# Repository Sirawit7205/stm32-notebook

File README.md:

# STM32 Notebook

This is an STM32 dev board that is designed to be put on a B6 ring binder notebook as covers. The board size is 130x180mm and contains 21 4mm ring holes.

**Note: I did tried to follow best practices as much as possible while designing this board, but it is still intended to be used as a notebook cover. The devices fitted might not work to their fullest spec. Please exercise caution.**

## Features - Front

The front side is the devboard. Featuring:

 - An STM32F103ZCT6 ARM-Cortex M3 Microcontroller in a 144-pin LQFP package
 - External 16MHz crystal and 32.768kHz RTC crystal
 - 2x IRS2003 H-Bridge Drivers with a pair of IRF7403 MOSFET (total of 2 drivers)
 - 2x PM8834 MOSFET Drivers with two IRF7403 MOSFETs in an Open-Drain configuration (total of 4 drivers)
 - 2x CD4050 Buffer for translating higher voltage logic inputs into STM32's 3.3v logic (total of 8 inputs)
 - 40x IO pins breakout
 - BOOT0/BOOT1 headers
 - SWD headers
 - Reset button
 - LM2596S-3.3 Buck Converter
 - Cute ponies

## Features - Back

The back side is a PCB footprint reference guide. Featuring:

 - Passive components (0201 to 1206)
 - Electrolytic Capacitors (3mm to 10mm)
 - JST connectors (GH, SH, PH, ...)
 - Diodes (MELF, SMA, SMB, SOD123, SOD323, ...)
 - Diode Bridges (ABS, MBS)
 - Transistors (SOT23, SOT223, LFPAK56, DPAK, ...)
 - Crystals (HC49, 0603 to 7050, 2 and 4 pins versions)
 - SOICs (SOIC4, SOIC8, SOIC14, SOIC16)
 - Wide SOICs (SOIC8W to SOIC28W)
 - TSSOPs (TSSOP8 to TSSOP40)
 - QFPs 0.5mm pitch (LQFP32 to LQFP144)
 - DFNs 0.4mm and 0.5mm pitch (DFN6 to DFN44)
 - QFNs 0.4mm pitch (QFN20 to QFN76)
 - QFNs 0.5mm pitch (QFN12 to QFN72)
 - More cute ponies
 
 ## Features - Latch
 
 This board features a pair of 20-pin Slide-Lock FFP Connectors, one on each side. These connectors are there so you can add a 20-pin Same-Side FFC Cable to act as a notebook closing strap.
 
 ## Licenses
 
 Hardware is licensed under `SPDX-License-Identifier: Apache-2.0 WITH SHL-2.1`
 
 This project is a certified Open Source Hardware. OSHWA UID TH000006.
 https://certification.oshwa.org/th000006.html
 
 ## Credits

 - 3215 Crystal model by Sam Ma: https://grabcad.com/library/crystal-smd-3215-pin2-1
 - Inductor model by Gydius: https://grabcad.com/library/inductor-wurth-elektronik-74437324100-1

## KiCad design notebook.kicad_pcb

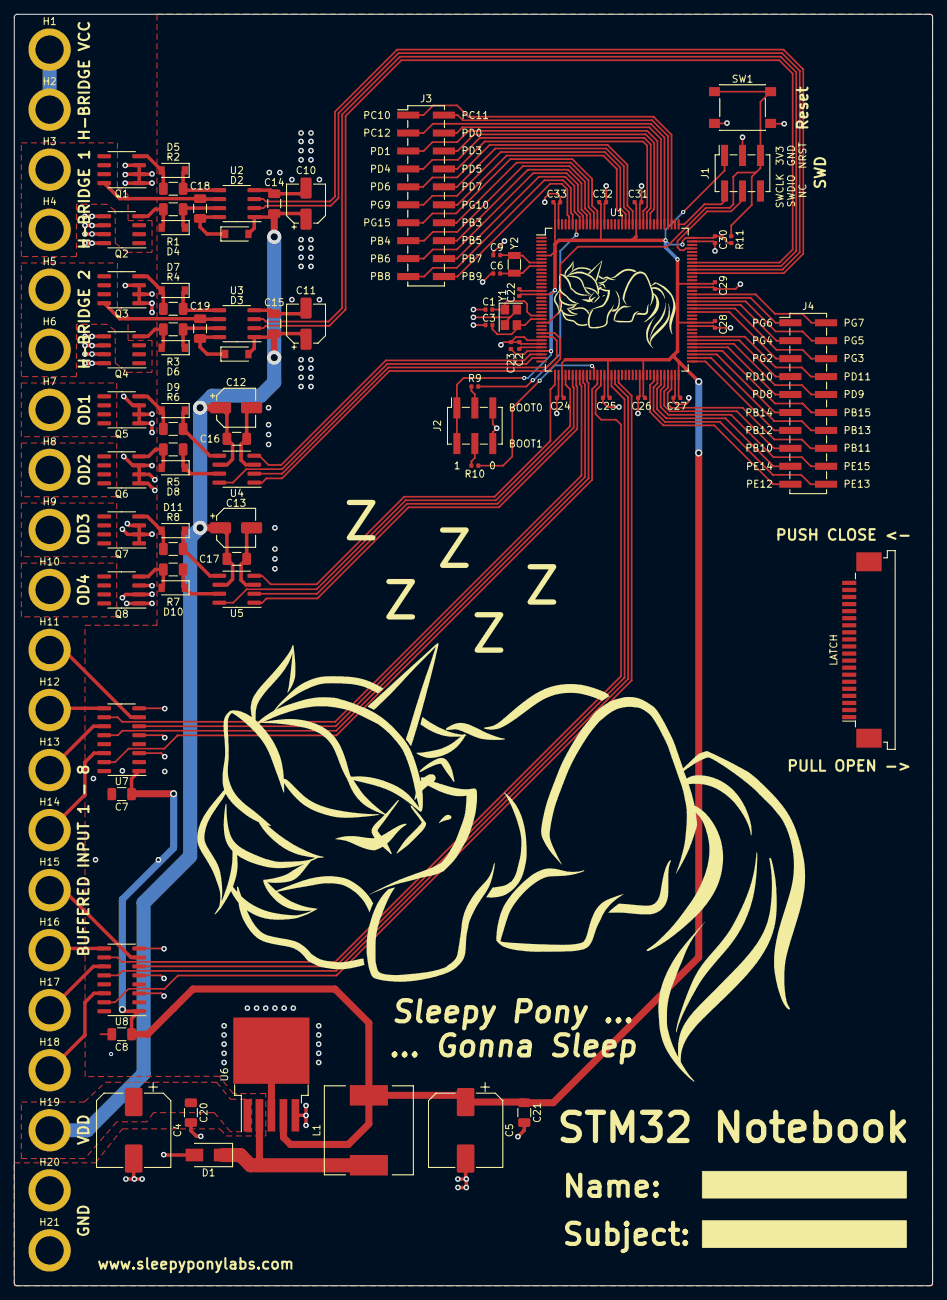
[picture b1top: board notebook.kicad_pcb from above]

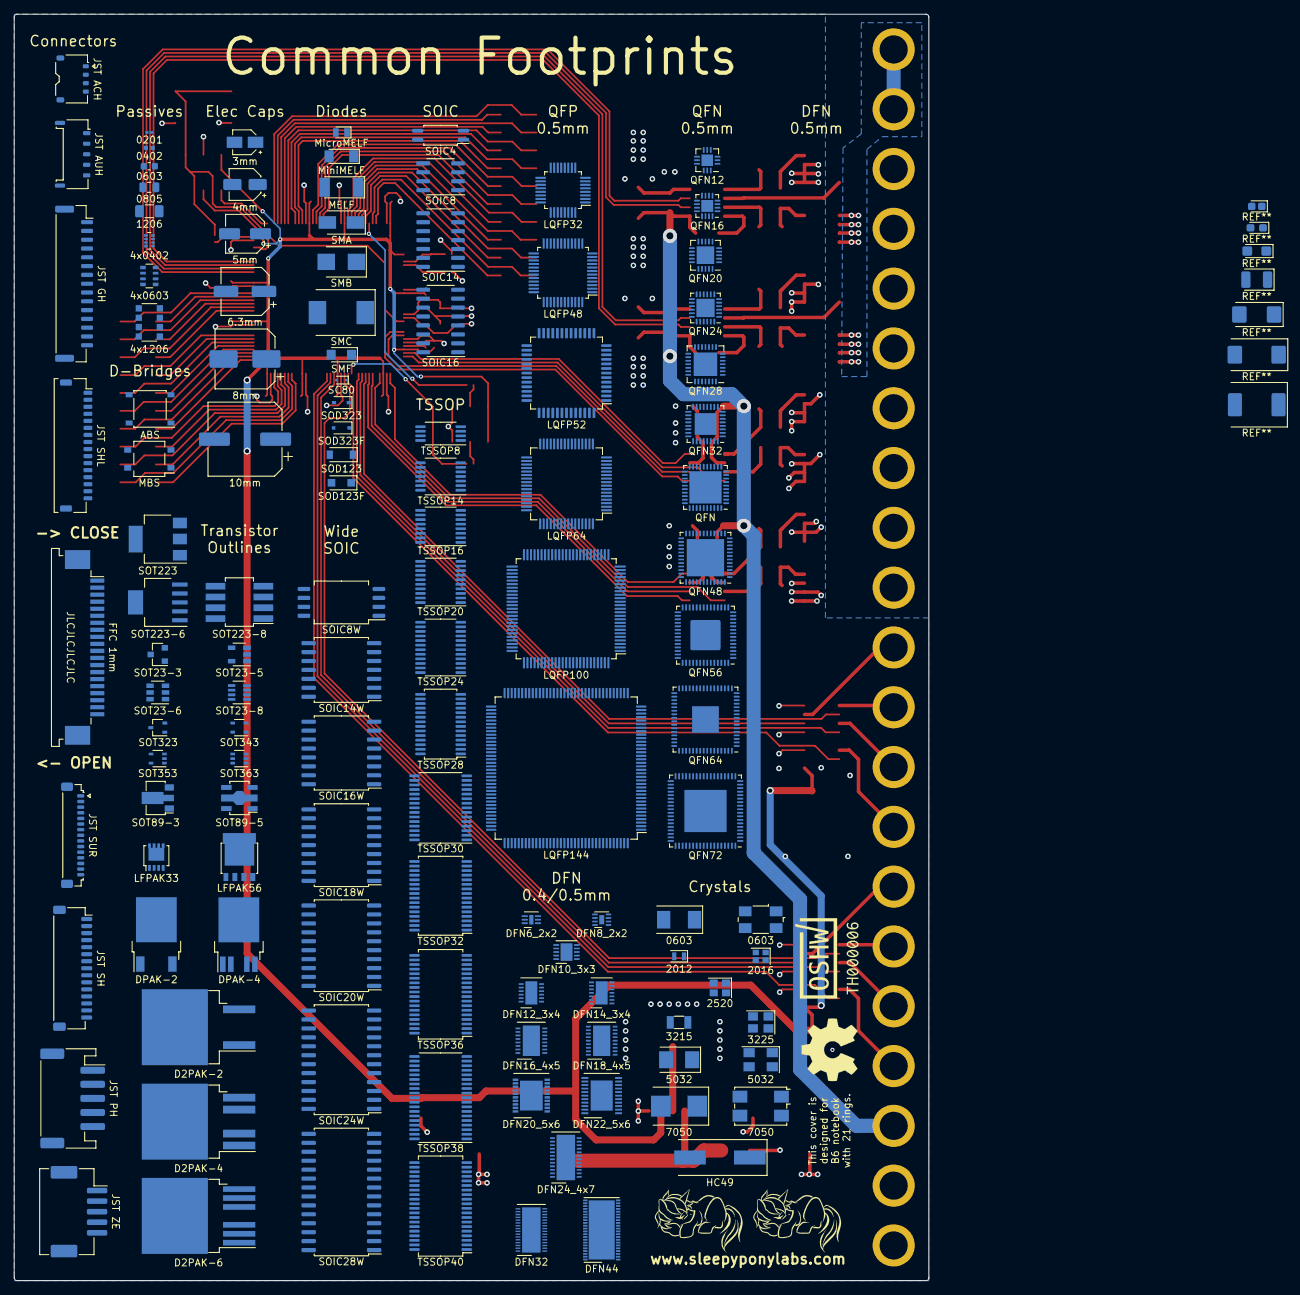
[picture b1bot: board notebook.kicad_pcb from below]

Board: 2 copper layers, 130.0 x 180.0 mm, 222 parts (121 on the bottom side), 109 nets.

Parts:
3mm: CP_Elec_3x5.3
4mm: CP_Elec_4x3
4x0402: R_Array_Convex_4x0402
4x0603: R_Array_Convex_4x0603
4x1206: R_Array_Convex_4x1206
5mm: CP_Elec_5x3
6.3mm: CP_Elec_6.3x3
8mm: CP_Elec_8x5.4
10mm: CP_Elec_10x7.7
0201: C_0201_0603Metric
0402: C_0402_1005Metric
0603: Crystal_SMD_0603-4Pin_6.0x3.5mm
0603#2: Crystal_SMD_0603-2Pin_6.0x3.5mm
0603#3: C_0603_1608Metric
0805: C_0805_2012Metric
1206: C_1206_3216Metric
2012: Crystal_SMD_2012-2Pin_2.0x1.2mm
2016: Crystal_SMD_2016-4Pin_2.0x1.6mm
2520: Crystal_SMD_2520-4Pin_2.5x2.0mm
3215: Crystal_SMD_3215-2Pin_3.2x1.5mm
3225: Crystal_SMD_3225-4Pin_3.2x2.5mm
5032: Crystal_SMD_5032-4Pin_5.0x3.2mm
5032#2: Crystal_SMD_5032-2Pin_5.0x3.2mm
7050: Crystal_SMD_7050-4Pin_7.0x5.0mm
7050#2: Crystal_SMD_7050-2Pin_7.0x5.0mm
ABS: Diode_Bridge_Diotec_ABS
C1, C3, C6, C9: 22pF; C_0402_1005Metric
C2: 10nF; C_0402_1005Metric
C4, C5: 220uF; CP_Elec_10x10
C7, C8, C14, C15, C16, C17, C20, C21: 100nF; C_1206_3216Metric
C10, C11, C12, C13: 10uF; CP_Elec_5x5.4
C18, C19: 1uF; C_1206_3216Metric
C22, C23, C24, C25, C26, C27, C28, C29, C30, C31, C32, C33: 100nF; C_0402_1005Metric
D1: SS34; D_SMA
D2, D3: FR107; D_SOD-123
D2PAK-2: TO-263-2
D2PAK-4: TO-263-4
D2PAK-6: TO-263-6
D4, D5, D6, D7, D8, D9, D10, D11: 1N4148; D_SOD-123
DFN6_2x2: DFN-6-1EP_2x2mm_P0.5mm_EP0.6x1.37mm
DFN8_2x2: DFN-8-1EP_2x2mm_P0.5mm_EP0.7x1.3mm
DFN10_3x3: DFN-10-1EP_3x3mm_P0.5mm_EP1.7x2.5mm
DFN12_3x4: DFN-12-1EP_3x4mm_P0.5mm_EP1.7x3.3mm
DFN14_3x4: DFN-14-1EP_3x4mm_P0.5mm_EP1.7x3.3mm
DFN16_4x5: DFN-16-1EP_4x5mm_P0.5mm_EP2.44x4.34mm
DFN18_4x5: DFN-18-1EP_4x5mm_P0.5mm_EP2.44x4.34mm
DFN20_5x6: DFN-20-1EP_5x6mm_P0.5mm_EP3.24x4.24mm
DFN22_5x6: DFN-22-1EP_5x6mm_P0.5mm_EP3.14x4.3mm
DFN24_4x7: DFN-24-1EP_4x7mm_P0.5mm_EP2.64x6.44mm
DFN32: DFN-32-1EP_4x7mm_P0.4mm_EP2.64x6.44mm
DFN44: DFN-44-1EP_5x8.9mm_P0.4mm_EP3.7x8.4mm
DPAK-2: TO-252-2
DPAK-4: TO-252-4
FFC 1mm: TE_2-84952-0_1x20-1MP_P1.0mm_Horizontal
H1, H2: VCCin; MountingHole_4mm_Pad_Thin
H3: HB1OUT1; MountingHole_4mm_Pad_Thin
H4: HB1OUT2; MountingHole_4mm_Pad_Thin
H5: HB2OUT1; MountingHole_4mm_Pad_Thin
H6: HB2OUT2; MountingHole_4mm_Pad_Thin
H7: OD1OUT; MountingHole_4mm_Pad_Thin
H8: OD2OUT; MountingHole_4mm_Pad_Thin
H9: OD3OUT; MountingHole_4mm_Pad_Thin
H10: OD4OUT; MountingHole_4mm_Pad_Thin
H11: ISOIN1; MountingHole_4mm_Pad_Thin
H12: ISOIN2; MountingHole_4mm_Pad_Thin
H13: ISOIN3; MountingHole_4mm_Pad_Thin
H14: ISOIN4; MountingHole_4mm_Pad_Thin
H15: ISOIN5; MountingHole_4mm_Pad_Thin
H16: ISOIN6; MountingHole_4mm_Pad_Thin
H17: ISOIN7; MountingHole_4mm_Pad_Thin
H18: ISOIN8; MountingHole_4mm_Pad_Thin
H19: VDDin; MountingHole_4mm_Pad_Thin
H20, H21: GND; MountingHole_4mm_Pad_Thin
HC49: Crystal_SMD_HC49-SD
J1: SWD; PinSocket_2x03_P2.54mm_Vertical_SMD
J2: BOOT; PinSocket_2x03_P2.54mm_Vertical_SMD
J3: ConnA; PinHeader_2x10_P2.54mm_Vertical_SMD
J4: ConnB; PinHeader_2x10_P2.54mm_Vertical_SMD
JST ACH: JST_ACH_BM04B-ACHSS-A-GAN-ETF_1x04-1MP_P1.20mm_Ve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; JST_ACH_BM04B-ACHSS-A-GAN-ETF_1x04-1MP_P1.20mm_Vertical
JST AUH: JST_AUH_BM05B-AUHKS-GA-TB_1x05-1MP_P1.50mm_Vertic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; JST_AUH_BM05B-AUHKS-GA-TB_1x05-1MP_P1.50mm_Vertical
JST GH: JST_GH_SM15B-GHS-TB_1x15-1MP_P1.25mm_Horizontal
JST PH: JST_PH_S5B-PH-SM4-TB_1x05-1MP_P2.00mm_Horizontal
JST SH: JST_SH_SM15B-SRSS-TB_1x15-1MP_P1.00mm_Horizontal
JST SHL: JST_SHL_SM16B-SHLS-TF_1x16-1MP_P1.00mm_Horizontal
JST SUR: JST_SUR_SM15B-SURS-TF_1x15-1MP_P0.80mm_Horizontal
JST ZE: JST_ZE_SM05B-ZESS-TB_1x05-1MP_P1.50mm_Horizontal
L1: 33uH; L_12x12mm_H8mm
LATCH: TE_2-84952-0_1x20-1MP_P1.0mm_Horizontal
LFPAK33: LFPAK33
LFPAK56: LFPAK56
LQFP32: LQFP-32_5x5mm_P0.5mm
LQFP48: LQFP-48_7x7mm_P0.5mm
LQFP52: LQFP-52_10x10mm_P0.65mm
LQFP64: LQFP-64_10x10mm_P0.5mm
LQFP100: LQFP-100_14x14mm_P0.5mm
LQFP144: LQFP-144_20x20mm_P0.5mm
MBS: TO-269AA
MELF: D_MELF
MicroMELF: D_MicroMELF
MiniMELF: D_MiniMELF
Q1, Q2, Q3, Q4, Q5, Q6, Q7, Q8: IRF7403; SOIC-8_3.9x4.9mm_P1.27mm
QFN: QFN-40-1EP_6x6mm_P0.5mm_EP4.6x4.6mm
QFN12: QFN-12-1EP_3x3mm_P0.5mm_EP1.65x1.65mm
QFN16: QFN-16-1EP_3x3mm_P0.5mm_EP1.7x1.7mm
QFN20: QFN-20-1EP_4x4mm_P0.5mm_EP2.5x2.5mm
QFN24: QFN-24-1EP_4x4mm_P0.5mm_EP2.6x2.6mm
QFN28: QFN-28-1EP_5x5mm_P0.5mm_EP3.35x3.35mm
QFN32: QFN-32-1EP_5x5mm_P0.5mm_EP3.1x3.1mm
QFN48: QFN-48-1EP_7x7mm_P0.5mm_EP5.3x5.3mm
QFN56: QFN-56-1EP_8x8mm_P0.5mm_EP4.3x4.3mm
QFN64: QFN-64-1EP_9x9mm_P0.5mm_EP3.8x3.8mm
QFN72: QFN-72-1EP_10x10mm_P0.5mm_EP6x6mm
R1, R2, R3, R4, R5, R6, R7, R8: 22R; R_1206_3216Metric
R9, R10, R11: 10K; R_0402_1005Metric
Ref**: Val**; TH000006_svg2sz
SC80: D_SC-80
SMA: D_SMA
SMB: D_SMB
SMC: D_SMC
SMF: D_SMF
SOD123: D_SOD-123
SOD123F: D_SOD-123F
SOD323: D_SOD-323
SOD323F: D_SOD-323F
SOIC4: SOIC-4_4.55x2.6mm_P1.27mm
SOIC8: SOIC-8_3.9x4.9mm_P1.27mm
SOIC8W: SOIC-8_7.5x5.85mm_P1.27mm
SOIC14: SOIC-14_3.9x8.7mm_P1.27mm
SOIC14W: SOIC-14W_7.5x9mm_P1.27mm
SOIC16: SOIC-16_3.9x9.9mm_P1.27mm
SOIC16W: SOIC-16W_7.5x10.3mm_P1.27mm
SOIC18W: SOIC-18W_7.5x11.6mm_P1.27mm
SOIC20W: SOIC-20W_7.5x12.8mm_P1.27mm
SOIC24W: SOIC-24W_7.5x15.4mm_P1.27mm
SOIC28W: SOIC-28W_7.5x17.9mm_P1.27mm
SOT23-3: SOT-23
SOT23-5: SOT-23-5
SOT23-6: SOT-23-6
SOT23-8: SOT-23-8
SOT89-3: SOT-89-3
SOT89-5: SOT-89-5
SOT223: SOT-223
SOT223-6: SOT-223-6
SOT223-8: SOT-223-8
SOT323: SOT-323_SC-70
SOT343: SOT-343_SC-70-4
SOT353: SOT-353_SC-70-5
SOT363: SOT-363_SC-70-6
SW1: RESET; SW_SPST_PTS645
TSSOP8: TSSOP-8_4.4x3mm_P0.65mm
TSSOP14: TSSOP-14_4.4x5mm_P0.65mm
TSSOP16: TSSOP-16_4.4x5mm_P0.65mm
TSSOP20: TSSOP-20_4.4x6.5mm_P0.65mm
TSSOP24: TSSOP-24_4.4x7.8mm_P0.65mm
TSSOP28: TSSOP-28_4.4x9.7mm_P0.65mm
TSSOP30: TSSOP-30_6.1x9.7mm_P0.65mm
TSSOP32: TSSOP-32_6.1x11mm_P0.65mm
TSSOP36: TSSOP-36_6.1x12.5mm_P0.65mm
TSSOP38: TSSOP-38_6.1x12.5mm_P0.65mm
TSSOP40: TSSOP-40_6.1x14mm_P0.65mm
U1: STM32F103ZCT6; LQFP-144_20x20mm_P0.5mm
U2, U3: IRS2003; SOIC-8_3.9x4.9mm_P1.27mm
U4, U5: PM8834; SOIC-8_3.9x4.9mm_P1.27mm
U6: LM2596S-3.3; TO-263-5_TabPin3
U7, U8: 4050; SOIC-16_3.9x9.9mm_P1.27mm
Y1: 16MHz; Crystal_SMD_3225-4Pin_3.2x2.5mm
Y2: 32.768kHz; Crystal_SMD_3215-2Pin_3.2x1.5mm

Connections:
+3V3: C5.1, C7.1, C8.1, C21.1, C22.1, C23.1, C24.1, C25.1, C26.1, C27.1, C28.1, C29.1, C30.1, C31.1, C32.1, C33.1, J1.1, J2.1, J2.2, L1.2, R11.1, U1.6, U1.17, U1.33, U1.39, U1.52, U1.62, U1.72, U1.84, U1.95, U1.108, U1.121, U1.131, U1.144, U6.4, U7.1, U8.1
BOOT0: R9.2, U1.138
BOOT1: R10.1, U1.48
CA1: J3.1, U1.111
CA2: J3.2, U1.112
CA3: J3.3, U1.113
CA4: J3.4, U1.114
CA5: J3.5, U1.115
CA6: J3.6, U1.117
CA7: J3.7, U1.118
CA8: J3.8, U1.119
CA9: J3.9, U1.122
CA10: J3.10, U1.123
CA11: J3.11, U1.124
CA12: J3.12, U1.125
CA13: J3.13, U1.132
CA14: J3.14, U1.133
CA15: J3.15, U1.134
CA16: J3.16, U1.135
CA17: J3.17, U1.136
CA18: J3.18, U1.137
CA19: J3.19, U1.139
CA20: J3.20, U1.140
CB1: J4.1, U1.91
CB2: J4.2, U1.92
CB3: J4.3, U1.89
CB4: J4.4, U1.90
CB5: J4.5, U1.87
CB6: J4.6, U1.88
CB7: J4.7, U1.79
CB8: J4.8, U1.80
CB9: J4.9, U1.77
CB10: J4.10, U1.78
CB11: J4.11, U1.75
CB12: J4.12, U1.76
CB13: J4.13, U1.73
CB14: J4.14, U1.74
CB15: J4.15, U1.69
CB16: J4.16, U1.70
CB17: J4.17, U1.67
CB18: J4.18, U1.68
CB19: J4.19, U1.65
CB20: J4.20, U1.66
GND: C1.2, C2.2, C3.2, C4.2, C5.2, C6.2, C7.2, C8.2, C9.2, C10.2, C11.2, C12.2, C13.2, C14.2, C15.2, C16.2, C17.2, C20.2, C21.2, C22.2, C23.2, C24.2, C25.2, C26.2, C27.2, C28.2, C29.2, C30.2, C31.2, C32.2, C33.2, D1.2, H20.1, H21.1, J1.3, J2.5, J2.6, Q1.1, Q1.2, Q1.3, Q3.1, Q3.2, Q3.3, Q5.1, Q5.2, Q5.3, Q6.1, Q6.2, Q6.3, Q7.1, Q7.2, Q7.3, Q8.1, Q8.2, Q8.3, SW1.2, U1.16, U1.30, U1.31, U1.38, U1.51, U1.61, U1.71, U1.83, U1.94, U1.107, U1.120, U1.130, U1.143, U2.4, U3.4, U4.3, U5.3, U6.3, U6.5, U7.3, U7.5, U7.8, U8.3, U8.5, U8.8, Y1.2, Y1.4
HB1IN1: U1.99, U2.2
HB1IN2: U1.98, U2.3
HB2IN1: U1.101, U3.2
HB2IN2: U1.100, U3.3
ISOIN1: U1.45, U7.6
ISOIN2: U1.44, U7.10
ISOIN3: U1.46, U7.12
ISOIN4: U1.49, U7.15
ISOIN5: U1.53, U8.6
ISOIN6: U1.50, U8.10
ISOIN7: U1.54, U8.12
ISOIN8: U1.55, U8.15
NRST: J1.5, R11.2, SW1.1, U1.25
unnamed: C1.1, U1.23, Y1.1
unnamed: C2.1, U1.32
unnamed: C3.1, U1.24, Y1.3
unnamed: C6.1, U1.9, Y2.2
unnamed: C9.1, U1.8, Y2.1
unnamed: C18.1, D2.1, U2.8
unnamed: C18.2, H3.1, H4.1, Q1.5, Q1.6, Q1.7, Q1.8, Q2.1, Q2.2, Q2.3, U2.6
unnamed: C19.1, D3.1, U3.8
unnamed: C19.2, H5.1, H6.1, Q3.5, Q3.6, Q3.7, Q3.8, Q4.1, Q4.2, Q4.3, U3.6
unnamed: D1.1, L1.1, U6.2
unnamed: D4.1, R1.1, U2.7
unnamed: D4.2, Q2.4, R1.2
unnamed: D5.1, R2.1, U2.5
unnamed: D5.2, Q1.4, R2.2
unnamed: D6.1, R3.1, U3.7
unnamed: D6.2, Q4.4, R3.2
unnamed: D7.1, R4.1, U3.5
unnamed: D7.2, Q3.4, R4.2
unnamed: D8.1, R5.1, U4.7
unnamed: D8.2, Q6.4, R5.2
unnamed: D9.1, R6.1, U4.5
unnamed: D9.2, Q5.4, R6.2
unnamed: D10.1, R7.1, U5.7
unnamed: D10.2, Q8.4, R7.2
unnamed: D11.1, R8.1, U5.5
unnamed: D11.2, Q7.4, R8.2
unnamed: H7.1, Q5.5, Q5.6, Q5.7, Q5.8
unnamed: H8.1, Q6.5, Q6.6, Q6.7, Q6.8
unnamed: H9.1, Q7.5, Q7.6, Q7.7, Q7.8
unnamed: H10.1, Q8.5, Q8.6, Q8.7, Q8.8
unnamed: H11.1, U7.7
unnamed: H12.1, U7.9
unnamed: H13.1, U7.11
unnamed: H14.1, U7.14
unnamed: H15.1, U8.7
unnamed: H16.1, U8.9
unnamed: H17.1, U8.11
unnamed: H18.1, U8.14
unnamed: J2.3, R9.1
unnamed: J2.4, R10.2
OD1EN: U1.28, U4.1
OD1IN: U1.29, U4.2
OD2EN: U1.35, U4.8
OD2IN: U1.34, U4.4
OD3EN: U1.43, U5.1
OD3IN: U1.42, U5.2
OD4EN: U1.40, U5.8
OD4IN: U1.37, U5.4
SWCLK: J1.2, U1.109
SWDIO: J1.4, U1.105
VCC: H1.1, H2.1, Q2.5, Q2.6, Q2.7, Q2.8, Q4.5, Q4.6, Q4.7, Q4.8
VDD: C4.1, C10.1, C11.1, C12.1, C13.1, C14.1, C15.1, C16.1, C17.1, C20.1, D2.2, D3.2, H19.1, U2.1, U3.1, U4.6, U5.6, U6.1

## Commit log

2021-02-09 Edit README and add pictures
2021-02-09 Edit README
2021-03-19 Add OSHWA mark
2023-02-04 WIP schematics
